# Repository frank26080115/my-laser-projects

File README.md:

# my-laser-projects
A bunch of stuff that can made on a laser cutter/engraver

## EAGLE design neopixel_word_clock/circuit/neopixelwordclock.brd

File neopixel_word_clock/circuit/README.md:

Circuit schematic and PCB are designed with CadSoft EAGLE 7

The part-list and component-placement-files are written to be directly uploaded to JLCPCB for full assembly service. The gerber files are provided and can be used with JLCPCB or any other PCB fabricator.

Some parts are missing and will have to be purchased separately from Digi-Key. Especially the 8x8 RGBW NeoPixel matrix board from Adafruit.

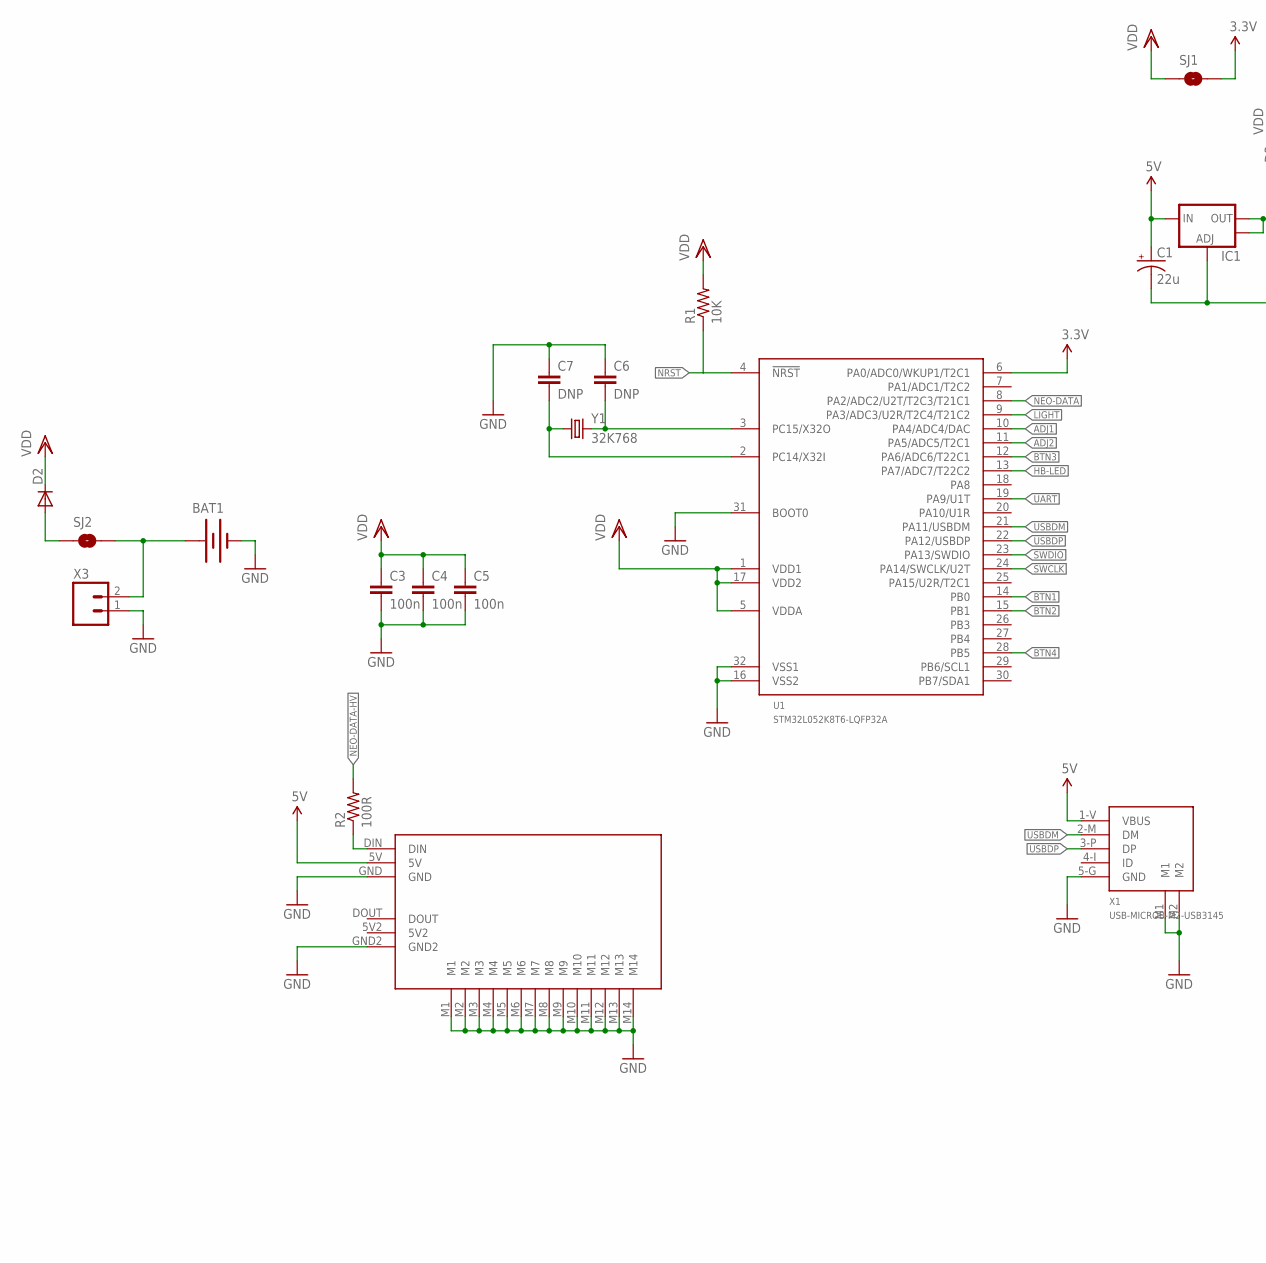
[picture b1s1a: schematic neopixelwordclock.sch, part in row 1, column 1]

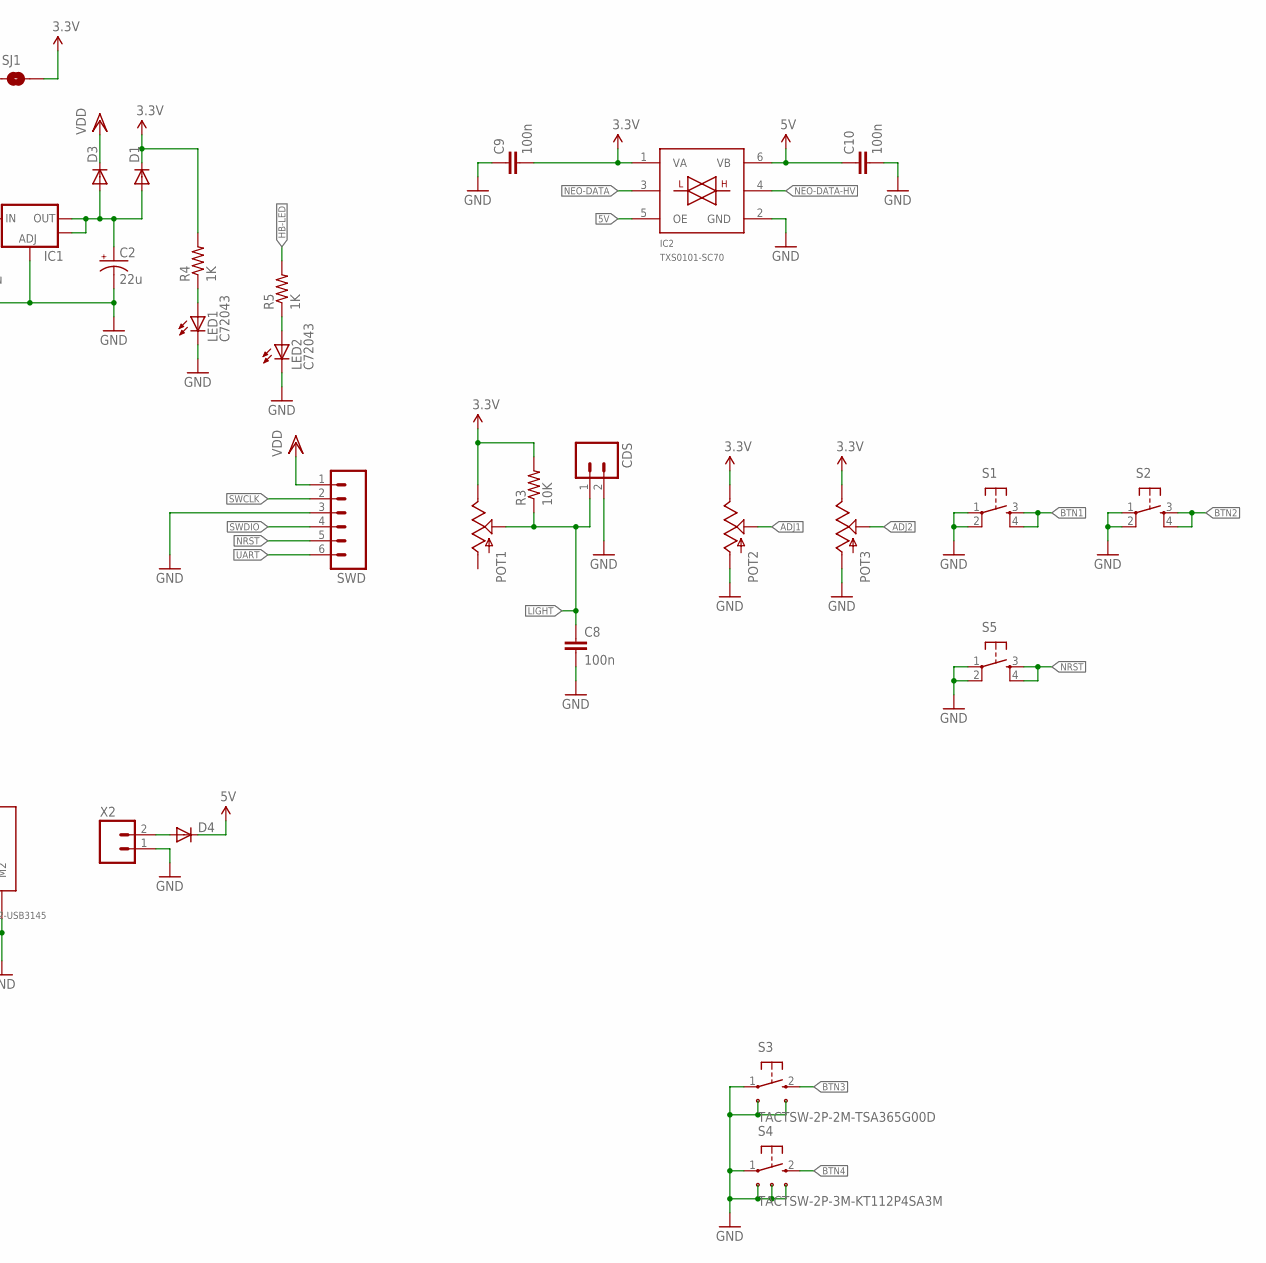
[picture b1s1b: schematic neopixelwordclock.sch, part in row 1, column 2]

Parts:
BAT1: BATTERY-JLC; BATT-COIN-CR2032-BS-6-1
C1, C2: 22u; EIA3528
C3, C4, C5, C8, C9, C10: 100n; 0603-CAP
C6, C7: DNP; 0603-CAP
CDS: M02PTH; 1X02
D1, D2, D3: DIODESOD; SOD-323
D4: DIODESMA; SMA-DIODE
IC1: V_REG_LM1117SOT223; SOT223
IC2: TXS0101-SC70; SC70-6
LED1, LED2: C72043; LED-0603
POT1, POT2, POT3: POT-SMD-A; POT-SMD
R1, R3: 10K; 0603-RES
R2: 100R; 0603-RES
R4, R5: 1K; 0603-RES
S1, S2, S5: TAC_SWITCHSMD; TACTILE_SWITCH_SMD
S3: TACTSW-2P-2M-TSA365G00D; TACTSW-SMD-SIDE-TSA365G00D
S4: TACTSW-2P-3M-KT112P4SA3M; TACTSW-SMD-SIDE-KT11P4SA3M
SJ1: SOLDERJUMPERNO; SJ_2S-NO
SJ2: SOLDERJUMPER-BIG; SJ_2S_BIG
SWD: M06FEMALE_LOCK; 1X06_FEMALE_LOCK.010
U1: STM32L052K8T6-LQFP32A; LQFP32
U$1: PCB-OUTLINE
X1: USB-MICROB-M2-USB3145; USBMICROBVERT-USB3145
X2, X3: M02-JST-2-PTH-NO_SILK; JST-2-PTH-NS
Y1: 32K768; XTAL-3.2X1.5

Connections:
3.3V: C9.2, D1.1 (C), IC2.1 (VA), POT1.A (B), POT2.A (B), POT3.A (B), R3.2, R4.2, SJ1.2, U1.6 (PA0/ADC0/WKUP1/T2C1)
5V: C1.A (+), C10.1, D4.C, IC1.3 (IN), IC2.5 (OE), IC2.6 (VB), U$1.5V, X1.1-V (VBUS)
ADJ1: POT2.W, U1.10 (PA4/ADC4/DAC)
ADJ2: POT3.W, U1.11 (PA5/ADC5/T2C1)
BTN1: S1.3, S1.4, U1.14 (PB0)
BTN2: S2.3, S2.4, U1.15 (PB1)
BTN3: S3.2, U1.12 (PA6/ADC6/T22C1)
BTN4: S4.2, U1.28 (PB5)
GND: BAT1.NEG (-), C1.C (-), C2.C (-), C3.2, C4.2, C5.2, C6.1, C7.1, C8.2, C9.1, C10.2, CDS.2, IC1.1 (ADJ), IC2.2 (GND), LED1.C, LED2.C, POT2.B (A), POT3.B (A), S1.1, S1.2, S2.1, S2.2, S3.1, S3.M1, S3.M2, S4.1, S4.M1, S4.M2, S4.M3, S5.1, S5.2, SWD.3, U1.16 (VSS2), U1.31 (BOOT0), U1.32 (VSS1), U$1.GND, U$1.GND2, U$1.M1, U$1.M2, U$1.M3, U$1.M4, U$1.M5, U$1.M6, U$1.M7, U$1.M8, U$1.M9, U$1.M10, U$1.M11, U$1.M12, U$1.M13, U$1.M14, X1.5-G (GND), X1.M1, X1.M2, X2.1, X3.1
HB-LED: R5.2, U1.13 (PA7/ADC7/T22C2)
LIGHT: C8.1, CDS.1, POT1.W, R3.1, U1.9 (PA3/ADC3/U2R/T2C4/T21C2)
unnamed: BAT1.POS (+), SJ2.2, X3.2
unnamed: C2.A (+), D1.2 (A), D3.2 (A), IC1.2 (OUT), IC1.4 (OUT)
unnamed: C6.2, U1.3 (PC15/X32O), Y1.2
unnamed: C7.2, U1.2 (PC14/X32I), Y1.1
unnamed: R2.1, U$1.DIN
unnamed: D4.A, X2.2
unnamed: D2.2 (A), SJ2.1
unnamed: LED2.A, R5.1
unnamed: LED1.A, R4.1
NEO-DATA: IC2.3 (A), U1.8 (PA2/ADC2/U2T/T2C3/T21C1)
NEO-DATA-HV: IC2.4 (B), R2.2
NRST: R1.1, S5.3, S5.4, SWD.5, U1.4 (!NRST)
SWCLK: SWD.2, U1.24 (PA14/SWCLK/U2T)
SWDIO: SWD.4, U1.23 (PA13/SWDIO)
UART: SWD.6, U1.19 (PA9/U1T)
USBDM: U1.21 (PA11/USBDM), X1.2-M (DM)
USBDP: U1.22 (PA12/USBDP), X1.3-P (DP)
VDD: C3.1, C4.1, C5.1, D2.1 (C), D3.1 (C), R1.2, SJ1.1, SWD.1, U1.1 (VDD1), U1.5 (VDDA), U1.17 (VDD2)

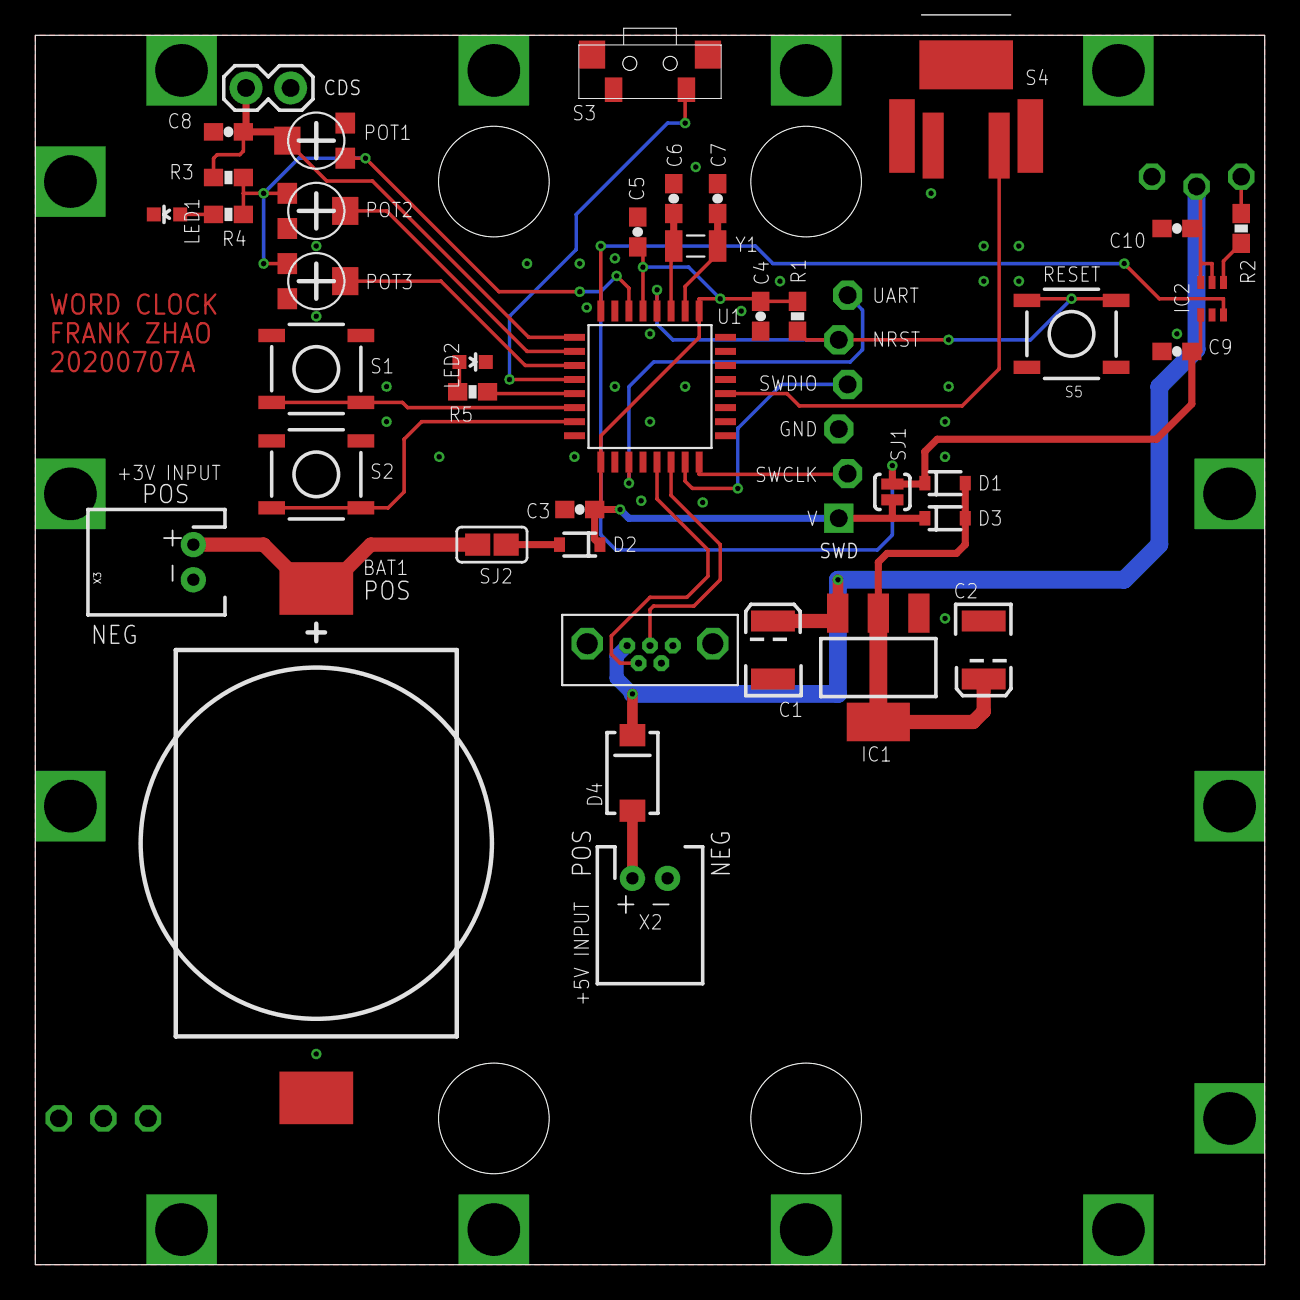
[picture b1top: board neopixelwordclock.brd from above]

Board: 2 copper layers, 70.0 x 70.0 mm, 42 parts (0 on the bottom side), 29 nets.

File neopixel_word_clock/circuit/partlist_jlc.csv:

2,"C1, C2",1210,22uF,C8020,"capacitor, tantalum"
6,"C3, C4, C5, C8, C9, C10",0604,100nF,C14663,"capacitor, chip"
3,"D1, D2, D3",SOD-323,,C146335,"diode, schotky"
1,D4,SMA,,C2480,"diode, schotky"
1,IC1,SOT-223,LM1117-3V3,C6186,v-reg
2,"R1, R3",0604,10Kê,C25804,"resistor, chip"
1,R2,0604,100ê,C22775,"resistor, chip"
2,"R4, R5",0604,1Kê,C21190,"resistor, chip"
3,"S1, S2, S5",TACT-SW,,C318886,tactile switch
1,U1,LQFP-32,STM32L052K8T6,C124724,MCU
1,Y1,XTAL-3.2x1.5,32.768 kHz,C32346,crystal
1,IC2,SC-70,TXS0101,C132031,v-translater
2,"LED1, LED2",0604,,C72043,
1,BAT1,,,C70377,battery

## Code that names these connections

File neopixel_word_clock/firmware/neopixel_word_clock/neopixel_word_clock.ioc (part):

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Mcu.Name=STM32L051K(6-8)Tx
Mcu.Package=LQFP32
Mcu.UserName=STM32L051K8Tx
PA0.Mode=SYS_WakeUp0
PA0.Signal=SYS_WKUP1
PA10.Mode=Asynchronous
PA10.Signal=USART1_RX
PA13.Mode=Serial_Wire
PA13.Signal=SYS_SWDIO
PA14.Mode=Serial_Wire
PA14.Signal=SYS_SWCLK
PA2.Signal=S_TIM2_CH3
PA3.Mode=IN3
PA3.Signal=ADC_IN3
PA4.Mode=IN4
PA4.Signal=ADC_IN4
PA5.Mode=IN5
PA5.Signal=ADC_IN5
PA6.GPIOParameters=GPIO_PuPd
PA6.GPIO_PuPd=GPIO_PULLUP
PA6.Signal=GPIO_Input
PA7.Signal=GPIO_Output
PA9.Mode=Asynchronous
PA9.Signal=USART1_TX
PB0.GPIOParameters=GPIO_PuPd
PB0.GPIO_PuPd=GPIO_PULLUP
PB0.Signal=GPIO_Input
PB1.GPIOParameters=GPIO_PuPd
PB1.GPIO_PuPd=GPIO_PULLUP
PB1.Signal=GPIO_Input
PB5.GPIOParameters=GPIO_PuPd
PB5.GPIO_PuPd=GPIO_PULLUP
PB5.Signal=GPIO_Input
PC14-OSC32_IN.Mode=LSE-External-Oscillator
PC14-OSC32_IN.Signal=RCC_OSC32_IN
PC15-OSC32_OUT.Mode=LSE-External-Oscillator
PC15-OSC32_OUT.Signal=RCC_OSC32_OUT
RCC.SYSCLKFreq_VALUE=32000000
RCC.SYSCLKSource=RCC_SYSCLKSOURCE_PLLCLK
board=custom

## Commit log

2020-06-25 orrey initial commit
2020-06-26 orrey - update tolerances, restructured SVG
2020-06-27 orrery - centered sun, fixed moon cut order
2020-06-27 orrery - removed extra pieces, reorganized
2020-06-28 orrery - tweaks after first attempt
2020-06-28 orrery - cad model added dowels, other binary changes unknown
2020-06-28 orrery - instructions and photos
2020-06-28 orrery - labels for instructions
2020-06-29 orrery - plug my own website twice
2020-07-11 word clock first upload
2020-07-14 word clock fixed bugs and removed USB
2020-07-14 word clock remove more USB files
2020-07-15 bahtinov_mask_67mm_filterthread
2020-07-15 bahtinov_mask_55mm_filterthread
2020-07-16 word clock change MCU to STM32F051
2020-07-18 word clock finalized documentation
2020-07-20 word clock code finalized, auto brightness added
2020-07-20 word clock, fixed auto brightness bug
2020-07-20 word clock, additional parts
2020-07-20 word clock, part list added screws
2020-07-21 word clock, fixed preserve row bug, better light change handling
2020-11-20 layered stars astro magnet
2020-11-20 update astro magnet doc
2020-11-23 update astro magnet docs
2020-12-09 update orrery readme with a picture
2020-12-09 astro magnet added pic to readme
